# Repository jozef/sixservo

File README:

NAME

    sixservo.ino - control 6 servo motors via serial console

SYNOPSIS

    after flashing into Arduino, connect via serial console 9600 to send
    commands:

        supported commands:
            sd [X] [int]             - turn servo to 0-180
            ss [X] [int]             - set puls width 500-2500
            sr [X] [int]             - set position relative to zero -1000-1000
            sweep [X] [int] [int]    - sweep servo [X] 0-180-0, optional count and step delay
            d [X]                    - detach / stop controlling the servo
            z [X]                    - set current as zero position
            c [X]                    - calibrate
            m [X] [int] [int]        - monitor servos, optional count and delay [s]
            save                     - save config
            dump [X]                 - show servo debug values
            ?                        - print this help
        [X] is servo index 1-6 or bitwise 000-077 (6 last bits as mask), default is zero -> 077
        ss 1 1500
        ok 1
        sd 0143 45
        ok 1
        ok 2
        ok 6

DESCRIPTION

    Serial console (19200) accepts commands and sets servo motor
    accordingly.

COMMANDS

    [X] is servo index 1-6 or bitwise 000-077 (6 last bits as mask),
    default is zero -> 077

 sd [X] [int] [int]

    Set servo angle. Value range 0 to 180.

 ss [X] [int] [int]

    Set servo angle using PWM peak time length in nano seconds. Value range
    500 to 2500.

sweep [X] [int] [int]

    Moves servo with index of first parameter from 90 to 180, then back to
    0 and again to 90 degree.

    Both parameters are optional. First is the number of repeats, default
    1. Second sets the time in milliseconds to wait between each angle
    change, default 15.

d [X]

    Will detach - stop sending PWM to servo, turning the control off.

z [X]

    Will set current servo position as zero.

c [X]

    Will calibrate servo -> calculate feedback be moving servo form current
    position back and forth.

m [X] [int] [int]

    Will monitor servos and return sr commands based on the feedback pin
    readings.

    Both paramters are optional. First parameter is the count of how many
    readings will be done. Use -1 or 0xffff to set infinite count. Will
    finish on any serial input. Second parameter is the delay between
    reading.

dump [X]

    Will dump servo data.

save [X]

    Will save servo data into eeprom for permanent storage.

rfst [X]

    Factory-reset will clear eeprom and start from defaults.

SEE ALSO

    KiCAD PCBs are here:
    https://github.com/jozef/sixservo/tree/master/KiCAD, first single servo
    version: https://blog.kutej.net/2020/04/servo-tester

LICENSE

    This is free software, licensed under the MIT License.

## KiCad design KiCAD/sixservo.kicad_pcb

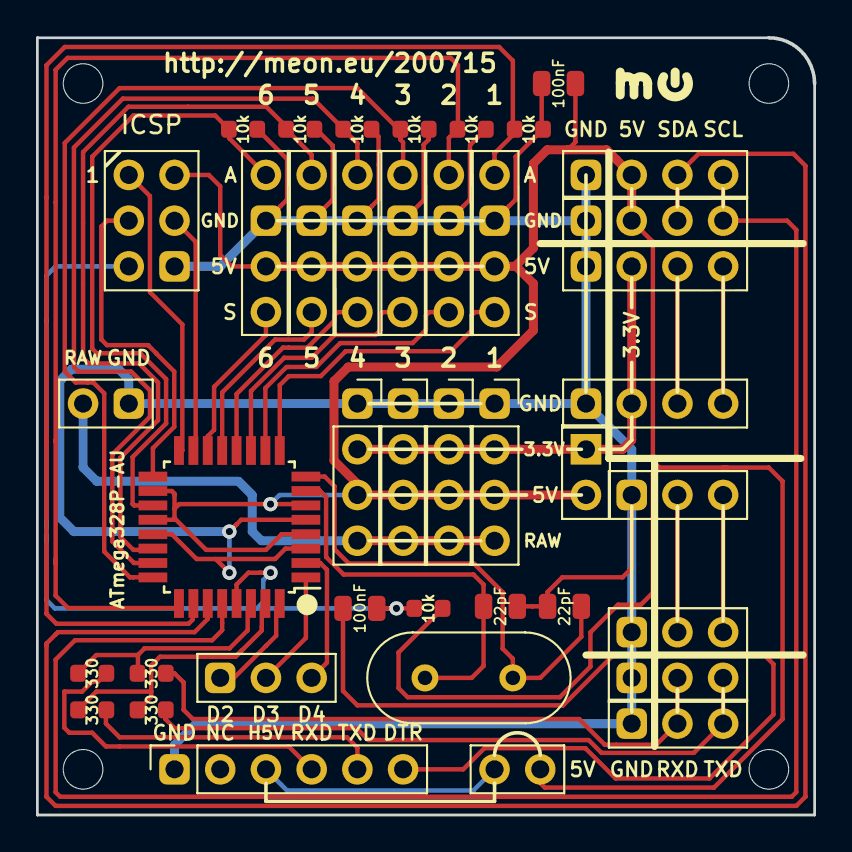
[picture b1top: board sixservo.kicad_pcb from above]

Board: 2 copper layers, 43.2 x 43.2 mm, 41 parts (0 on the bottom side), 39 nets.

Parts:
C0, C2: 100nF; C_0805_2012Metric_no_lines
C11, C12: 22pF; C_0805_2012Metric_no_lines
J0: ICSP; PinHeader_2x03_P2.54mm_Vertical_closed
J1: USB_to_TTL; PinSocket_1x06_P2.54mm_Vertical
J5: extra_pins; PinSocket_1x03_P2.54mm_Vertical_closed
J21: servo1; PinHeader_1x04_P2.54mm_Vertical_closed
J22: servo2; PinHeader_1x04_P2.54mm_Vertical_closed
J23: servo3; PinHeader_1x04_P2.54mm_Vertical_closed
J24: servo4; PinHeader_1x04_P2.54mm_Vertical_closed
J25: servo5; PinHeader_1x04_P2.54mm_Vertical_closed
J26: servo6; PinHeader_1x04_P2.54mm_Vertical_closed
J33: i2c-3.3; PinHeader_1x04_P2.54mm_Vertical_closed
J35: i2c-5; PinHeader_1x04_P2.54mm_Vertical_closed
J43: serial-3.3; PinHeader_1x03_P2.54mm_Vertical_closed
J45: serial-5; PinHeader_1x03_P2.54mm_Vertical_closed
J91, J92, J93, J94: Power; PinSocket_1x04_P2.54mm_Vertical
J95, J97: Power; PinHeader_1x02_P2.54mm_Vertical_closed
J332: i2c-3.3_2; PinHeader_1x04_P2.54mm_Vertical_closed
J352: i2c-5_2; PinHeader_1x04_P2.54mm_Vertical_closed
J432: serial-3.3_2; PinHeader_1x03_P2.54mm_Vertical_closed
J452: serial-5_2; PinHeader_1x03_P2.54mm_Vertical_closed
JP9: hdr_5v; PinHeader_1x02_P2.54mm_Vertical_closed
R1, R21, R22, R23, R24, R25, R26: 10k; R_0603_1608Metric_no_lines
R12, R13, R14, R15: 330; R_0603_1608Metric_no_lines
U1: ATmega328P-AU; TQFP-32_7x7mm_P0.8mm
Y1: 16MHz; Crystal_HC49-U_Vertical

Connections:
+3V3: J33.2, J91.2, J92.2, J93.2, J94.2, J97.1, J332.2
+5V: C0.1, J0.2, J21.2, J22.2, J23.2, J24.2, J25.2, J26.2, J35.2, J91.3, J92.3, J93.3, J94.3, J97.2, J352.2, JP9.1, R1.1, U1.4, U1.6, U1.18, U1.20
A0: J24.4, R24.1, U1.23
A1: J23.4, R23.1, U1.24
A2: J22.4, R22.1, U1.25
A3: J21.4, R21.1, U1.26
A6: J26.4, R26.1, U1.19
A7: J25.4, R25.1, U1.22
D2: J5.1, U1.32
D3: J5.2, U1.1
D4: J5.3, U1.2
D5: J21.1, U1.9
D6: J22.1, U1.10
D7: J23.1, U1.11
D8: J24.1, U1.12
D9: J25.1, U1.13
D10: J26.1, U1.14
D11_MOSI: J0.4, U1.15
D12_MISO: J0.1, U1.16
D13_SCK: J0.3, U1.17
DTR: C2.2, J1.6
GND: C0.2, C11.1, C12.2, J0.6, J1.1, J21.3, J22.3, J23.3, J24.3, J25.3, J26.3, J33.1, J35.1, J43.1, J45.1, J91.1, J92.1, J93.1, J94.1, J95.1, J332.1, J352.1, J432.1, J452.1, R21.2, R22.2, R23.2, R24.2, R25.2, R26.2, U1.3, U1.5, U1.21
unnamed: C11.2, U1.7, Y1.2
unnamed: C12.1, U1.8, Y1.1
unnamed: J1.3, JP9.2
unnamed: J1.4, R12.2
unnamed: J1.5, R13.2
RAW: J91.4, J92.4, J93.4, J94.4, J95.2
RXD: R12.1, R14.1, U1.30
RXD_3: J43.2, J432.2
RXD_P: J45.2, J452.2, R14.2
SCL: J35.4, J352.4, U1.28
SCL_3: J33.4, J332.4
SDA: J35.3, J352.3, U1.27
SDA_3: J33.3, J332.3
TXD: R13.1, R15.1, U1.31
TXD_3: J43.3, J432.3
TXD_P: J45.3, J452.3, R15.2
~RST: C2.1, J0.5, R1.2, U1.29

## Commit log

2020-06-24 initial version
2020-07-04 s/ATmega328PB/ATmega328P/, add TX/RX protective resistors
2020-07-15 initial 6servo control code
2020-07-16 add raw+gnd pins for power shield
2020-07-18 add more commands
2020-07-18 endless monitor possible, save/load/reset config from eeprom
2020-10-03 simpliefied servo index octets mask, more docu, faster monitoring stop
2020-10-05 flush serial before monitoring loop
2020-10-05 add movement mirroring example script
2020-10-05 typooo
2020-10-21 log and replay servo movements
2020-10-25 allow for fluent movements
2020-10-25 tag/label first version
